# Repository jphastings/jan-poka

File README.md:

# Jan Poka

A device for bringing your distant friends a little nearer.

## Set up

Use docker to run anywhere:

```bash
docker run --env-file .env --network host ghcr.io/jphastings/jan-poka:latest
```

NB. You must run attached to the host network, as this service uses Bonjour service discovery, so needs to know its network-visible IP address.

(Assuming that you have appropriate environment variables in a file called `.env`)

## Options

While executing:

| $ENV_VAR            | Functionality                                                                                                                       |
|---------------------|-------------------------------------------------------------------------------------------------------------------------------------|
| $JP_HOMELATITUDE    | The latitude of where the device is.                                                                                                |
| $JP_HOMELONGITUDE   | The longitude of where the device is.                                                                                               |
| $JP_HOMEALTITUDE    | The altitude of where the device is.                                                                                                |
| $JP_MQTTPORT        | The port to run the MQTT broker on.                                                                                                 |
| $JP_USEAUDIO        | Allows audio playing — used by text-to-speech. (Requires [libasound2-dev](https://packages.debian.org/sid/libasound2-dev) on Linux) |

While building:

| build tag | Functionality                                                                        |
|-----------|--------------------------------------------------------------------------------------|
| libnova   | Allows celestial body location (Requires [libnova](http://libnova.sourceforge.net/)) |

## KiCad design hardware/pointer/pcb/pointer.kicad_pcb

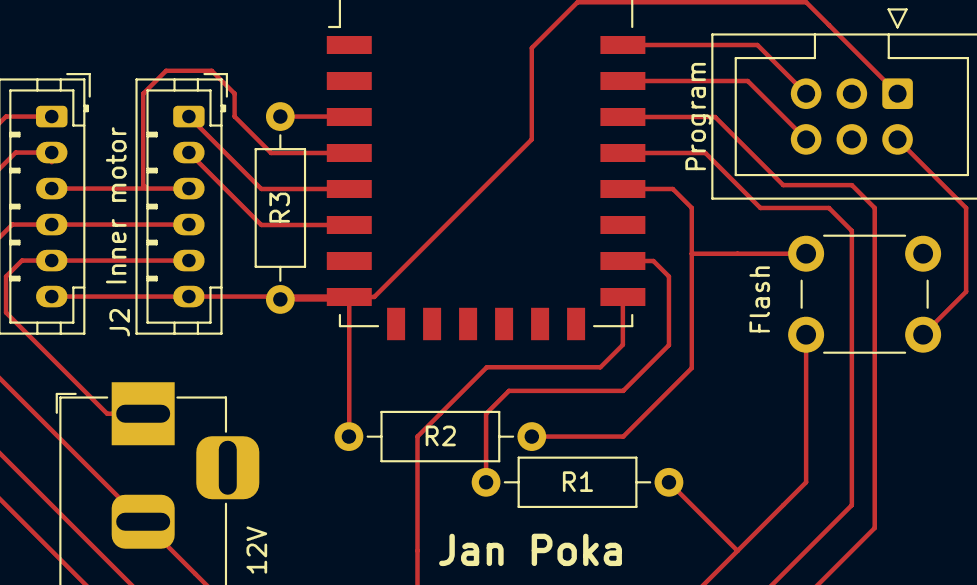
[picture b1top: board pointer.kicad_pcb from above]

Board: 2 copper layers, 9 parts (0 on the bottom side), 13 nets.

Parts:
DC: 12V; BarrelJack_Horizontal
J1: Outer Motor; JST_PH_B6B-PH-K_1x06_P2.00mm_Vertical
J2: Inner motor; JST_PH_B6B-PH-K_1x06_P2.00mm_Vertical
J3: Program; IDC-Header_2x03_P2.54mm_Vertical
R1, R2, R3: 10k; R_Axial_DIN0207_L6.3mm_D2.5mm_P10.16mm_Horizontal
SW: Flash; SW_PUSH_6mm_H4.3mm
U1: ESP-12E

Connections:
+3V3: J1.6, J2.6, J3.1, R2.2, R3.2, U1.8
GND: DC.2, J1.4, J2.4, J3.2, R1.1, SW.2, U1.15
unnamed: DC.1, J1.5, J2.5
unnamed: J1.1, U1.20
unnamed: J1.2, U1.19
unnamed: J1.3, J2.3, U1.4
unnamed: J2.1, U1.5
unnamed: J2.2, U1.6
unnamed: J3.5, U1.22
unnamed: J3.6, U1.21
unnamed: R1.2, U1.16
unnamed: R2.1, SW.1, U1.18
unnamed: R3.1, U1.3

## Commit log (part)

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2018-08-13 Basic Corviator
2018-08-26 tweaks
2018-08-27 Add tests for transforms
2018-08-27 Use types to ensure correct degrees/radians/meters
2018-08-27 Tests demonstrating failure in relative direction
2018-08-27 Fix types
2018-08-28 Use real transforms and coordinate systems to make life _easy_.
2018-08-28 Comments!
2018-08-29 Test tweaks.
2018-10-16 Improve structure, maybe?
2018-12-30 Swap to lower case
2018-12-30 Trials with Balena
2018-12-30 Balena Dockerfile
2018-12-30 Can't get remote repos
2018-12-30 Vendor libs
2018-12-30 Copy all files to docker
2018-12-30 Fix docker repo
2018-12-30 Use real base image
2018-12-30 Try stepper
2018-12-30 Logging
2018-12-30 More logs
2018-12-30 Faster…
2018-12-30 Use the right pin number…
2018-12-30 Stepper method
2018-12-30 Correct locations for local libs
2018-12-30 Logs
2018-12-30 More space
2018-12-30 Looper
2018-12-30 ooops
2018-12-30 Only 90º
2018-12-30 Randomness
2019-01-02 Sleep motor inbetween turns
2019-01-02 Try speeding up the rotation
2019-01-02 Tweak pulse times
2019-01-02 Slow down the pulsing
2019-01-02 Switch to quarter stepping
2019-01-02 A little faster on the quarter step
2019-01-02 What about much lower?
2019-01-02 Not quite so fast, pause before & after sleeping
2019-01-02 A little slower…
2019-01-03 Refactor for Balena
    Support for the RPi; refactor to allow different plugins, set up just the one motor for now.
2019-01-03 Expose http port
    Exposes an HTTP port within the container
2019-01-03 Fix over-eager gitignore
2019-01-03 Deliveroo isn't ready yet!
2019-01-03 Maybe I need to update?
2019-01-03 Try just asound
2019-01-03 Disabling TTS support for now
2019-01-03 Support Motor Sleeping
    Automatically sleep the motors after movement is complete. Currently might cause trouble, as it's done with timing rather than actual promises.
    If the motor stepping takes longer than estimated then the non-promise system in place will have trouble and the motors will be powered down before the steps are complete.
2019-01-03 EnvVar configurable autosleep
    Make auto-sleep leeway a configurable duration
2019-01-03 Debug logging
    Somethings up, the stepper is going _very_ slowly — let's see what's going on!
2019-01-03 Debug logging
    We're stepping very slowly, wonder why!
2019-01-03 Failing to rotate with any strength
    Something is up with the timing, sending some more logging
2019-01-03 Swap to a channel/promise type system
    Use channels as a way of scheduling the motor movements without innaccurate timing
2019-01-03 Swap to using names not greek letters
    Greek letters are cool and all, but no-one knows which one's which, and they raise warnings in the compiler 😅
2019-01-03 Unfocus tests
    A test was focused on, allow all tests to run.
2019-01-03 Create concept of Futures
    `nil` values sent down a channel don't unblock the channel, so create an object to pass down (called `future.Result`) and some helper methods to work with them (`future.Future` etc)
2019-01-03 Add newline to log output
2019-01-03 Log about which trackers are being used
2019-01-05 Adding new types for celestial coordinates
2019-01-05 C wrapper library for Celestial positions
    Uses libnova for calculating rough positions for the major celestial bodies.
2019-01-05 More understandable distances
2019-01-05 Add libnova dependency to Dockerfile
2019-01-05 Remove libnova work for now
2019-01-05 Temporarily remove celestial
2019-01-05 Remove TTS links
2019-01-05 Debug time!
2019-01-06 Better file naming
    Make it clearer which files are being loaded by build tags.
2019-01-06 It's debug time again
2019-01-06 Log errors with presentation
2019-01-06 Error logging
2019-01-06 More debug
2019-01-06 Ugh, I do not know what I'm doing
2019-01-06 Strip out unnecessary complexity
2019-01-06 Remove debug logging
2019-01-06 Fix typo
    Ensure we declare that we're powering _down_ the motors.
2019-11-16 Rename
2019-11-16 Instagram?
2019-11-17 Tower control
2019-11-21 Looks like it's working with steppers!
2019-11-22 Extract direction picker
2019-11-22 Move TTS to new structure
2019-11-22 Audio tweaks
2019-12-25 Models! Directions!
    Should have fixed directions, also models included!
2019-12-26 ADS-B, Bonjour, Go Mod
2021-04-11 Havne't been committing...
2021-04-11 Scrub password & make more readable
    Ugh; don't leave passwords in codebases, eh? Password swapped, and moved to environment variable gathering.
2021-04-11 Add MQTT
    Adds publishing both the target Lat/Long and the AER coords to MQTT.
2021-04-11 Added instagram source
    Will grab the lat long of a recent instagram post
2021-04-11 Fix comments
2021-04-11 Enabled Immediate HTTP response
    Allows there to be an immediate response of the target location over the HTTP channel, if one returns fast enough.
2021-04-11 Enabled Google Maps search
    Also implements Elevation API lookup.
2021-04-11 Fix response casing
2021-04-11 Allow hardware folder again
2021-04-11 Informative HTTP responses
2021-04-11 Add concentric gear pointer device
    Adds the Arduino code for Chris' concertic gear pointer device, written for esp8266
2021-04-11 No need for the scratch folder
2021-04-11 Try to fix speed matching
2021-04-12 Swap to multi-app structure
    Controller now lives in `cmd/controller/`.
2021-04-12 Try out environs
2021-04-13 Swap to server build Dockerfile
2021-04-13 Fix build issues
2021-04-13 Swap to proper port, to avoid clashes
2021-04-13 Add temporary logo
2021-04-17 Swap to hardcoded credentials
2021-04-17 Rename to simpler
2021-04-17 Add KiCAD designs
2021-04-30 Start combining other repos
    - Contains all current 3d models
    - Contains initial (very incomplete) PCB designs
    - Contains vendored OpenSCAD repos, for the 3d models
2021-04-30 Remove direct RPi tooling
    Jan Poka has become a server, with lower powered devices controlling the stepper motors (as they're more capable of controlling them smoothly, and without issues)
    I've removed the 'tower' information, but this commit remains if I ever wish to bring it back.
2021-04-30 Allow unique MQTT names (per host)
    As MQTT disconnects multiple clients of the same ID.
2021-05-02 Refactor to allow provider-driven halting of repeat
2021-05-02 Stop retrying if a provider fails
    Ensures that Deliveroo status isn't repeatedly polled if it has already been delivered.
2021-05-02 Swap ADS-B to be dynamically configured
2021-05-02 Rename ADS-B package to stop IDE complaining
2021-05-02 Reorder directories for clarity
2021-05-03 Refactor Location return type
2021-05-03 First part of pointer model; joint
2021-05-04 First pass at working timing belt
2021-05-08 Woking timing belt
2021-05-14 Improve pointer; arrow not right yet
2021-09-01 Add Mapper maths & framework for web mapper.
2021-09-01 Refactor for no global state
2021-09-02 Compiling, but projection not functional
2021-09-02 Safe & clean shutdowns
2021-09-06 Fix map projection system
    Proj wasn't well documented enough to be able to use easily. Swapped to a simpler (and likely less accurate, but still viable) library.
2021-09-07 Adds mapper setup tool
2021-12-31 Add Clock
2021-12-31 Keep vars.h secret from now on
2021-12-31 Move to Platformio style
2021-12-31 Move to main.cpp
2021-12-31 Working with MQTT
2022-01-02 Not quite complete calibration
2022-01-02 It works!
    Also added OpenSCAD files for clock hands.
2022-01-03 Move 2dpoints to vendor folder
2022-01-03 Vendor folder ignored in github
2022-01-05 Fix tests & migrate to new Go
2022-01-05 Support time in phrase tracker
2022-01-06 Ship time details with MQTT message
    Adds:
    - Local time (HH:MM:SS)
    - UTC offset (for setting up local NTP instances)
    - (Omits Daylight savings time offset at the moment; is this needed?)
    - "Sky Changes" ie. the different phases of day/night/twilight, and minutes offset from the most recent local midnight for the next 24 hours from now.
    Sky Changes may eventually also hold weather information.
2022-01-06 Calculate and ship time details with MQTT message (#2)
    Adds:
    - Local time (HH:MM:SS)
    - UTC offset (for setting up local NTP instances)
    - (Omits Daylight savings time offset at the moment; is this needed?)
    - "Sky Changes" ie. the different phases of day/night/twilight, and minutes offset from the most recent local midnight for the next 24 hours from now.
    Sky Changes may eventually also hold weather information.
2022-01-06 Bump to v1.17 of go
2022-01-06 Smaller JSON keys
2022-01-06 Shrink Docker image
2022-01-06 Fix MQTT message size overload for clock
2022-01-08 Publish docker containers to Github
2022-01-08 Fix publish action
2022-01-08 Add Unraid application template
    Also adds an icon for the suite.
2022-01-08 Flag as Beta app
2022-01-09 Fix XML errors
2022-01-09 Fix UNraid XML
2022-01-09 Migrate pointer to platformio
2022-01-09 Migrate mapper placeholder project to platformio
2022-01-09 Tweak pointer for functionality
2022-01-09 Swap to using fractional days for sky changes
2022-01-09 Bump version number
2022-01-09 Calculate sunrise/set on device
2022-01-09 No need for API url
2022-01-09 Retain MQTT messages so restarting devices are accurate
2022-01-09 Fix typo failures
2022-01-09 Remove unnecessary packages
2022-01-09 Move openscad to ext
2022-01-09 Bump version for mapper
2022-01-09 no need for -mod=mod
2022-01-09 Prevent binaries from being added
2022-01-09 Fix missing submodules
2022-01-09 Fix name of github action
2022-01-10 In-built MQTT server
    - Generalizes mDNS
    - Swaps to shutdown manager
    - Removes much MQTT config that's now unneeded
2022-01-11 Adds auto-versioning
2022-01-11 Adds auto-versioning (#4)
2022-01-11 Build on push
    Currently broken because variables are needed on build. I'll need to find an on-device way to configure MQTT settings etc.
2022-01-11 Attempts to move to Bonjour-based set up
    I have a sneaking suspicion this laptop doesn't support mDNS properly.
2022-01-19 Fixed mDNS
2022-01-19 Build on push (#3)
    * Build on push & bonjour-based set up of clock
2022-01-19 Bumping versions from #3
    These are the new version numbers:
    - (whole repository): 0.8.0
2022-01-19 Name & bump version of tagger
2022-01-19 Improve workflow name
2022-01-19 Swap to on create tags
    This should trigger when PRs are merged via bump version bumper
2022-01-19 Readme improvement (#5)
2022-01-19 Bumping versions from #5
    These are the new version numbers:
    - (whole repository): 0.8.1
2022-01-19 Remove gocv for now
    Debian doesn't support it, which is breaking container builds
2022-01-19 Remove gocv for now (#6)
    Debian doesn't support it, which is breaking container builds
2022-01-19 Bumping versions from #6
    These are the new version numbers:
    - (whole repository): 0.8.2
2022-01-19 Fix build on push
    The `create` trigger runs on every ref that's created (irrespective of the `tags` filter below).
    Switch back to `push` while I debug why this isn't working.
2022-01-19 Tweak to trigger build with PR
2022-01-19 Tweak to trigger build with PR (#7)
2022-01-19 Bumping versions from #7
    These are the new version numbers:
    - (whole repository): 0.8.3
2022-01-20 Ensure triggering of other workflows
    Follow-on workflows require a PAT instead of the default token.
2022-01-20 Fixes docker builds
2022-01-20 Fixes docker builds (#8)
2022-01-20 Bump version
2022-01-20 Allow choosing specific interface for mDNS (later all)
2022-01-20 Allow choosing specific interface for mDNS (later all) (#9)
2022-01-21 Add timeout to Google queries
2022-01-21 Add timeout to Google queries (#14)
2022-01-21 Bumping versions from #14
    These are the new version numbers:
    - (whole repository): 0.8.6
2022-06-22 Assorted projector pieces
2022-06-22 Projector into modules
2022-06-24 Embed Earth Lights
    Embeds the earth lights image from NASA into the binary.
2022-06-24 Write to screenbuffer
2022-06-25 Pi & mac OS; draw directly
    Drawing directly to the platform's drawable, so there's limited delay in getting the pixels to the screen on mac os (and there's hope for speeding up the display on the pi!)
